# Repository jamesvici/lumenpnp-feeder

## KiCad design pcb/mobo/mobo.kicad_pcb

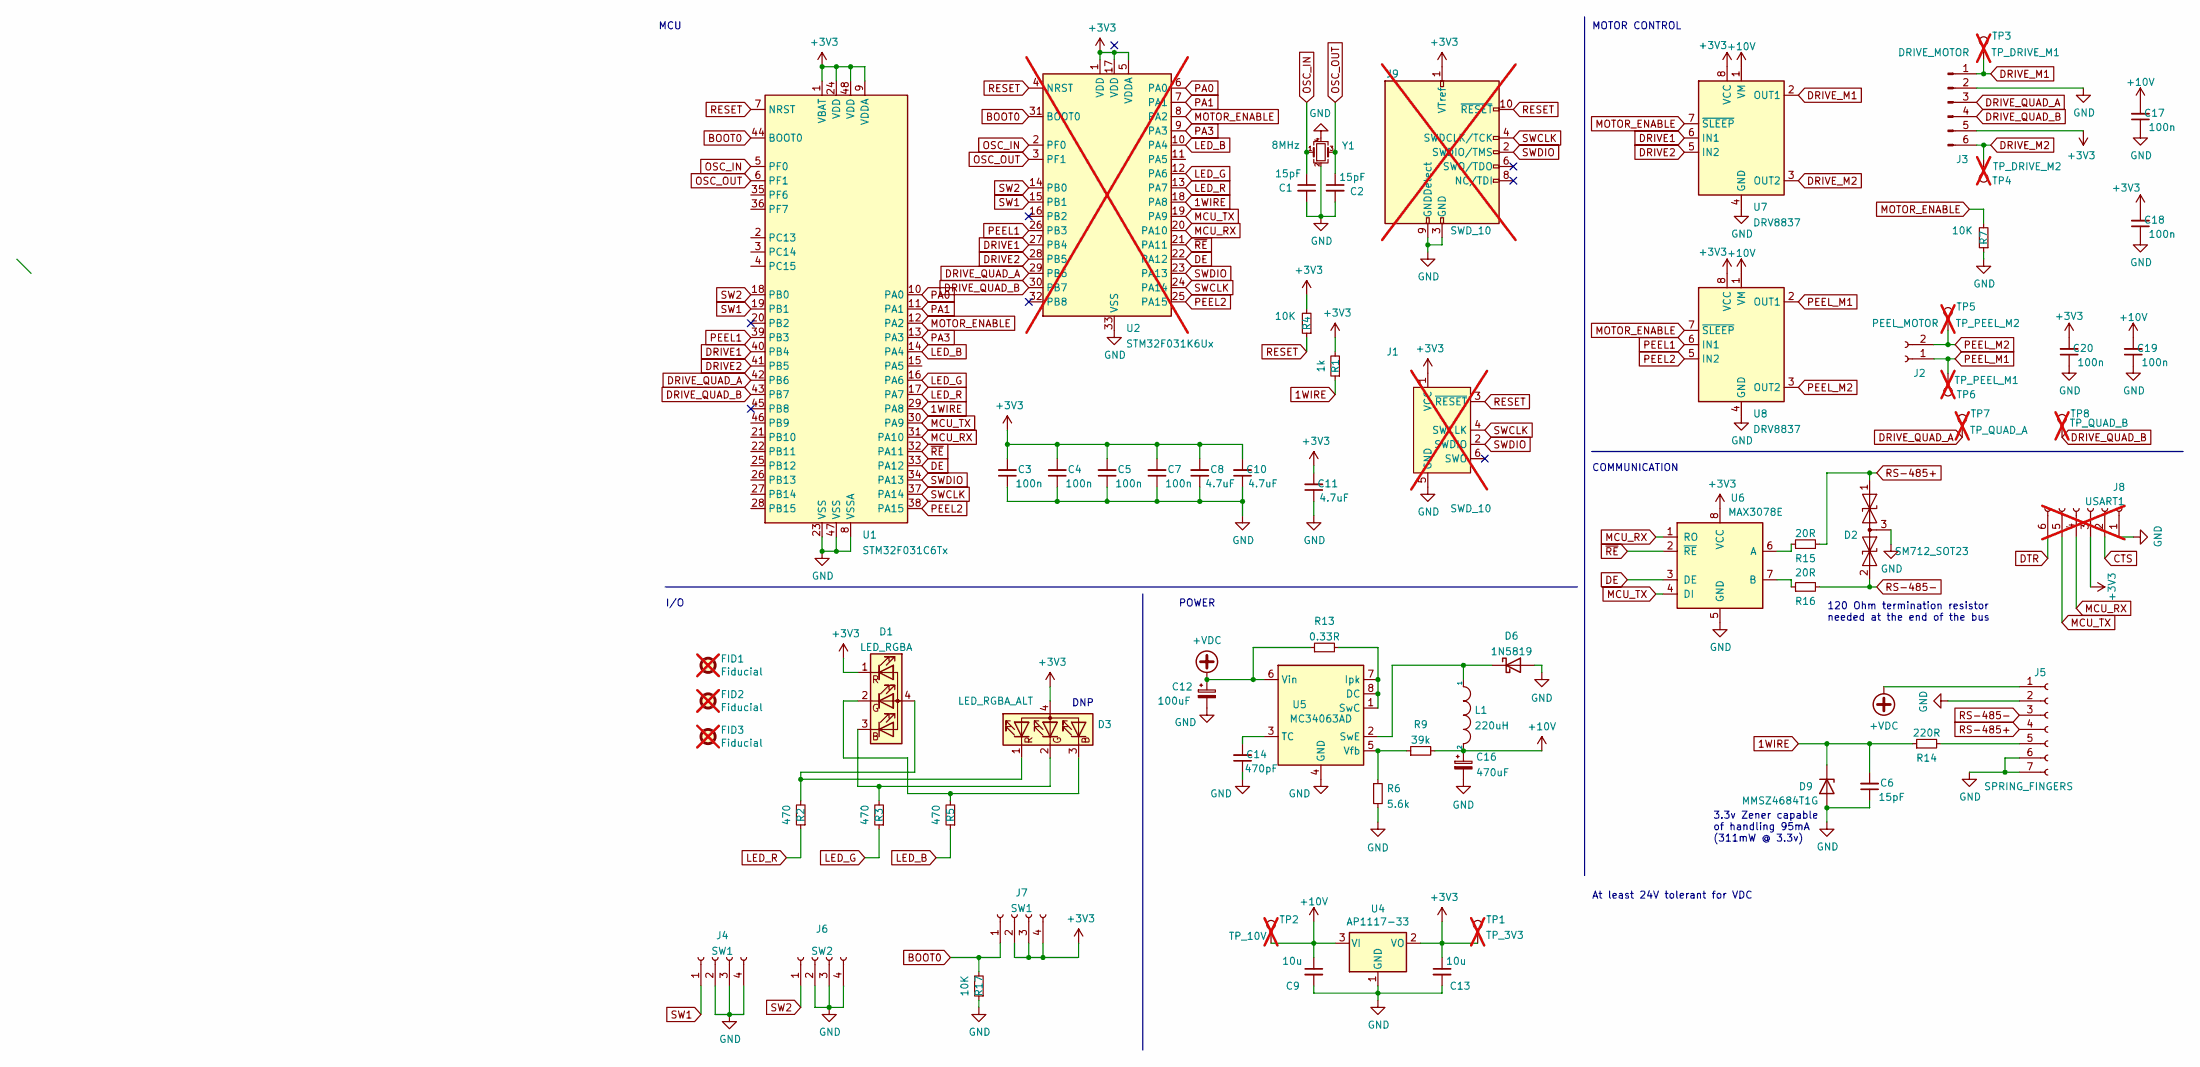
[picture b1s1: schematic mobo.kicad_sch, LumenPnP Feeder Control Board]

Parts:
C1, C2, C6: 15pF; C_0805_2012Metric; LCSC C527077
C3, C4, C5, C7, C17, C18, C19, C20: 100n; C_0805_2012Metric; LCSC C476766
C8, C10, C11: 4.7uF; C_0805_2012Metric; LCSC C1779
C9, C13: 10u; C_0805_2012Metric; LCSC C15850
C12: 100uF; C_Elec_6.3x7.7; LCSC C178512
C14: 470pF; C_0805_2012Metric; LCSC C1743
C16: 470uF; C_Elec_8x6.2; LCSC C5354997
D1: LED_RGBA; MHS110FRGBCT; DigiKey 732-11414-1-ND
D2: SM712_SOT23; SOT-23; LCSC C521963
D3: LED_RGBA_ALT; LED_LiteOn_LTST-C19HE1WT; LCSC C458749
D6: 1N5819; D_SOD-323_HandSoldering; DigiKey 1655-1N5819WCT-ND
D9: MMSZ4684T1G; D_SOD-123; DigiKey MMSZ4684T1GOSCT-ND
FID1, FID2, FID3: Fiducial; Fiducial_1mm_Mask2mm; not fitted
J1: SWD_10; Tag-Connect_TC2030-IDC-FP_2x03_P1.27mm_Vertical; not fitted
J2: PEEL_MOTOR; Molex_PicoBlade_53261-0271_1x02-1MP_P1.25mm_Horizontal; LCSC C2845379
J3: DRIVE_MOTOR; Molex_PicoBlade_53261-0671_1x06-1MP_P1.25mm_Horizontal; LCSC C2845383
J4, J7: SW1; 1TS003B-1400-3500A-CT; LCSC C319392
J5: SPRING_FINGERS; AVX-9155-005-541; DigiKey 478-5453-1-ND
J6: SW2; 1TS003B-1400-3500A-CT; LCSC C319392
J8: USART1; UART_FRICTION_FIT; not fitted
J9: SWD_10; PinHeader_2x05_P1.27mm_Vertical_SMD; DigiKey 1528-5434-ND; not fitted
L1: 220uH; L_6.3x6.3_H3; LCSC C5127556
R1: 1k; R_0805_2012Metric; LCSC C17513
R2, R3, R5: 470; R_0805_2012Metric; LCSC C119076
R4, R7, R17: 10K; R_0805_2012Metric; LCSC C84376
R6: 5.6k; R_0805_2012Metric; LCSC C4382
R9: 39k; R_0805_2012Metric; LCSC C113306
R13: 0.33R; R_0805_2012Metric; DigiKey 13-RT0805FRE0733RLCT-ND
R14: 220R; R_0805_2012Metric; DigiKey 13-RT0805FRE07220RLCT-ND
R15, R16: 20R; R_0805_2012Metric; DigiKey 311-20.0CRCT-ND
TP1: TP_3V3; TestPoint_Pad_D2.0mm; not fitted
TP2: TP_10V; TestPoint_Pad_D2.0mm; not fitted
TP3: TP_DRIVE_M1; TestPoint_Pad_D2.0mm; not fitted
TP4: TP_DRIVE_M2; TestPoint_Pad_D2.0mm; not fitted
TP5: TP_PEEL_M2; TestPoint_Pad_D2.0mm; not fitted
TP6: TP_PEEL_M1; TestPoint_Pad_D2.0mm; not fitted
TP7: TP_QUAD_A; TestPoint_Pad_D2.0mm; not fitted
TP8: TP_QUAD_B; TestPoint_Pad_D2.0mm; not fitted
U1: STM32F031C6Tx; LQFP-48_7x7mm_P0.5mm; LCSC C329281
U2: STM32F031K6Ux; QFN-32-1EP_5x5mm_P0.5mm_EP3.45x3.45mm; not fitted
U4: AP1117-33; SOT-223-3_TabPin2; LCSC C5250992
U5: MC34063AD; SOIC-8_3.9x4.9mm_P1.27mm; LCSC C100023
U6: MAX3078E; SOIC-8_3.9x4.9mm_P1.27mm; LCSC C336020
U7, U8: DRV8837; WSON-8-1EP_2x2mm_P0.5mm_EP0.9x1.6mm; DigiKey 296-34806-1-ND
Y1: 8MHz; Crystal_SMD_3225-4Pin_3.2x2.5mm_HandSoldering; LCSC C5308002

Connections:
1WIRE: C6.2, D9.1 (K), R1.1, R14.1, U1.29 (PA8), U2.18 (PA8)
+3V3: C3.2, C4.2, C5.2, C7.2, C8.2, C10.2, C11.2, C13.1, C18.2, C20.2, D1.1 (RK), D3.4 (A), J1.1 (VCC), J3.5, J7.2, J7.3, J7.4, J8.3, J9.1 (VTref), R1.2, R4.2, TP1.1, U1.1 (VBAT), U1.9 (VDDA), U1.24 (VDD), U1.48 (VDD), U2.1 (VDD), U2.5 (VDDA), U2.17 (VDD), U4.2 (VO), U6.8 (VCC), U7.8 (VCC), U8.8 (VCC)
+10V: C9.1, C16.1, C17.2, C19.2, L1.2, R9.2, TP2.1, U4.3 (VI), U7.1 (VM), U8.1 (VM)
+VDC: C12.1, J5.1, R13.1, U5.6 (Vin)
BOOT0: J7.1, R17.2, U1.44 (BOOT0), U2.31 (BOOT0)
CTS: J8.2
DE: U1.33 (PA12), U2.22 (PA12), U6.3 (DE)
DRIVE1: U1.40 (PB4), U2.27 (PB4), U7.6 (IN1)
DRIVE2: U1.41 (PB5), U2.28 (PB5), U7.5 (IN2)
DRIVE_M1: J3.1, TP3.1, U7.2 (OUT1)
DRIVE_M2: J3.6, TP4.1, U7.3 (OUT2)
DRIVE_QUAD_A: J3.3, TP7.1, U1.42 (PB6), U2.29 (PB6)
DRIVE_QUAD_B: J3.4, TP8.1, U1.43 (PB7), U2.30 (PB7)
DTR: J8.6
GND: C1.2, C2.2, C3.1, C4.1, C5.1, C6.1, C7.1, C8.1, C9.2, C10.1, C11.1, C12.2, C13.2, C14.1, C16.2, C17.1, C18.1, C19.1, C20.1, D2.3 (common), D6.2 (A), D9.2 (A), J1.5 (GND), J3.2, J4.2, J4.3, J4.4, J5.2, J5.6, J5.7, J6.2, J6.3, J6.4, J8.1, J9.3 (GND), J9.5 (GND), J9.9 (GNDDetect), R6.2, R7.1, R17.1, U1.8 (VSSA), U1.23 (VSS), U1.47 (VSS), U2.33 (VSS), U4.1 (GND), U5.4 (GND), U6.5 (GND), U7.4 (GND), U7.9 (GND), U8.4 (GND), U8.9 (GND), Y1.2, Y1.4
LED_B: R5.1, U1.14 (PA4), U2.10 (PA4)
LED_G: R3.1, U1.16 (PA6), U2.12 (PA6)
LED_R: R2.1, U1.17 (PA7), U2.13 (PA7)
MCU_RX: J8.4, U1.31 (PA10), U2.20 (PA10), U6.1 (RO)
MCU_TX: J8.5, U1.30 (PA9), U2.19 (PA9), U6.4 (DI)
MOTOR_ENABLE: R7.2, U1.12 (PA2), U2.8 (PA2), U7.7 (~SLEEP), U8.7 (~SLEEP)
unnamed: D1.4 (A), D3.1 (RK), R2.2
unnamed: D1.3 (BK), D3.2 (GK), R3.2
unnamed: D1.2 (GK), D3.3 (BK), R5.2
unnamed: D6.1 (K), L1.1, U5.2 (SwE)
unnamed: J5.5, R14.2
unnamed: R13.2, U5.1 (SwC), U5.7 (Ipk), U5.8 (DC)
unnamed: C14.2, U5.3 (TC)
unnamed: R6.1, R9.1, U5.5 (Vfb)
unnamed: R15.1, U6.6 (A)
unnamed: R16.1, U6.7 (B)
OSC_IN: C1.1, U1.5 (PF0), U2.2 (PF0), Y1.1
OSC_OUT: C2.1, U1.6 (PF1), U2.3 (PF1), Y1.3
PA0: U1.10 (PA0), U2.6 (PA0)
PA1: U1.11 (PA1), U2.7 (PA1)
PA3: U1.13 (PA3), U2.9 (PA3)
PEEL1: U1.39 (PB3), U2.26 (PB3), U8.6 (IN1)
PEEL2: U1.38 (PA15), U2.25 (PA15), U8.5 (IN2)
PEEL_M1: J2.1, TP6.1, U8.2 (OUT1)
PEEL_M2: J2.2, TP5.1, U8.3 (OUT2)
RESET: J1.3 (~RESET), J9.10 (~RESET), R4.1, U1.7 (NRST), U2.4 (NRST)
RS-485+: D2.1 (A1), J5.4, R15.2
RS-485-: D2.2 (A2), J5.3, R16.2
SW1: J4.1, U1.19 (PB1), U2.15 (PB1)
SW2: J6.1, U1.18 (PB0), U2.14 (PB0)
SWCLK: J1.4 (SWCLK), J9.4 (SWDCLK/TCK), U1.37 (PA14), U2.24 (PA14)
SWDIO: J1.2 (SWDIO), J9.2 (SWDIO/TMS), U1.34 (PA13), U2.23 (PA13)
~RE: U1.32 (PA11), U2.21 (PA11), U6.2 (~RE)

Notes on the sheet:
I/O
DNP
COMMUNICATION
MOTOR CONTROL
POWER
3.3v Zener capable of handling 95mA (311mW @ 3.3v)
At least 24V tolerant for VDC
MCU
120 Ohm termination resistor needed at the end of the bus

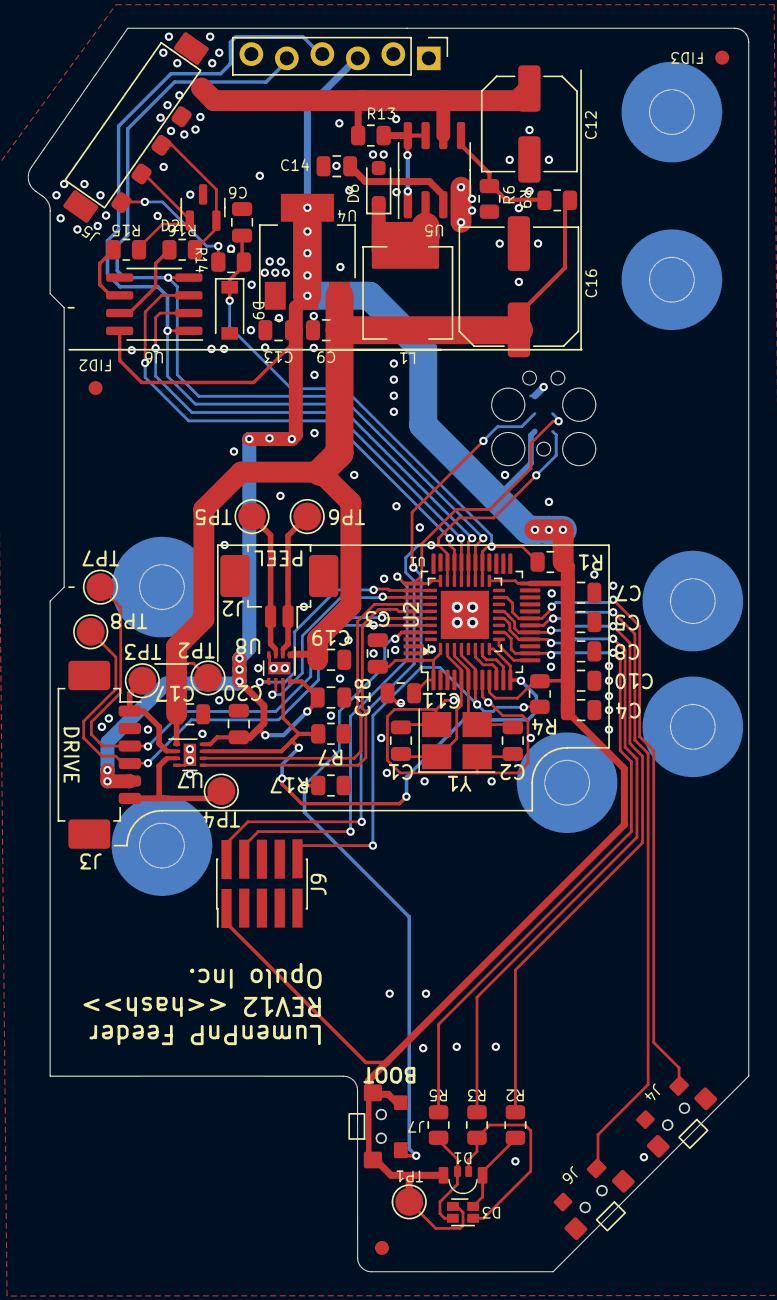
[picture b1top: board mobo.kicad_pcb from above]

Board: 2 copper layers, 51.6 x 89.0 mm, 66 parts (1 on the bottom side), 46 nets.

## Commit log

2025-02-14 updates asm to show latest frame changes
2025-03-15 Change 470uF electrolytic from 6.3mm to 8mm so there are more options available; Add LCSC, Mouser, and DigiKey reference parts.
2025-03-15 Add jlcpcb to .gitignore as a precaution.
2025-03-17 Invalid LCSC part for crystal, changed to C527077
2025-03-17 Convert SWD connector on back to TC2030. Left one on front for Adafruit 5434 connector.
2025-03-26 Modify SWD footprint to make compatible with Adafruit 5434
